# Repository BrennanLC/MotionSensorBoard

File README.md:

Motion Sensor Board
==============

Wireless motion sensor board that interfaces with parallax PIR sensor.
Board uses the Attiny2313A microcontroller. wireless capability provided by Xbee Pro Series 2 module.

Current version of motion sensor board verified on 9/28/14

Files:

MotionSensorsch.pdf - Copy of board schematic in PDF format
MotionSensorBoard.sch - Board schematic eagle file 
MotionSensorBoard.brd - Board layout eagle file
MotionSensorBoard.pdf - Board layout in PDF format
Gerbers.zip - Gerber board files

schematic and board layout built with Eagle 6.4.0 Standard. More info and 
download available here:

https://www.cadsoftusa.com/

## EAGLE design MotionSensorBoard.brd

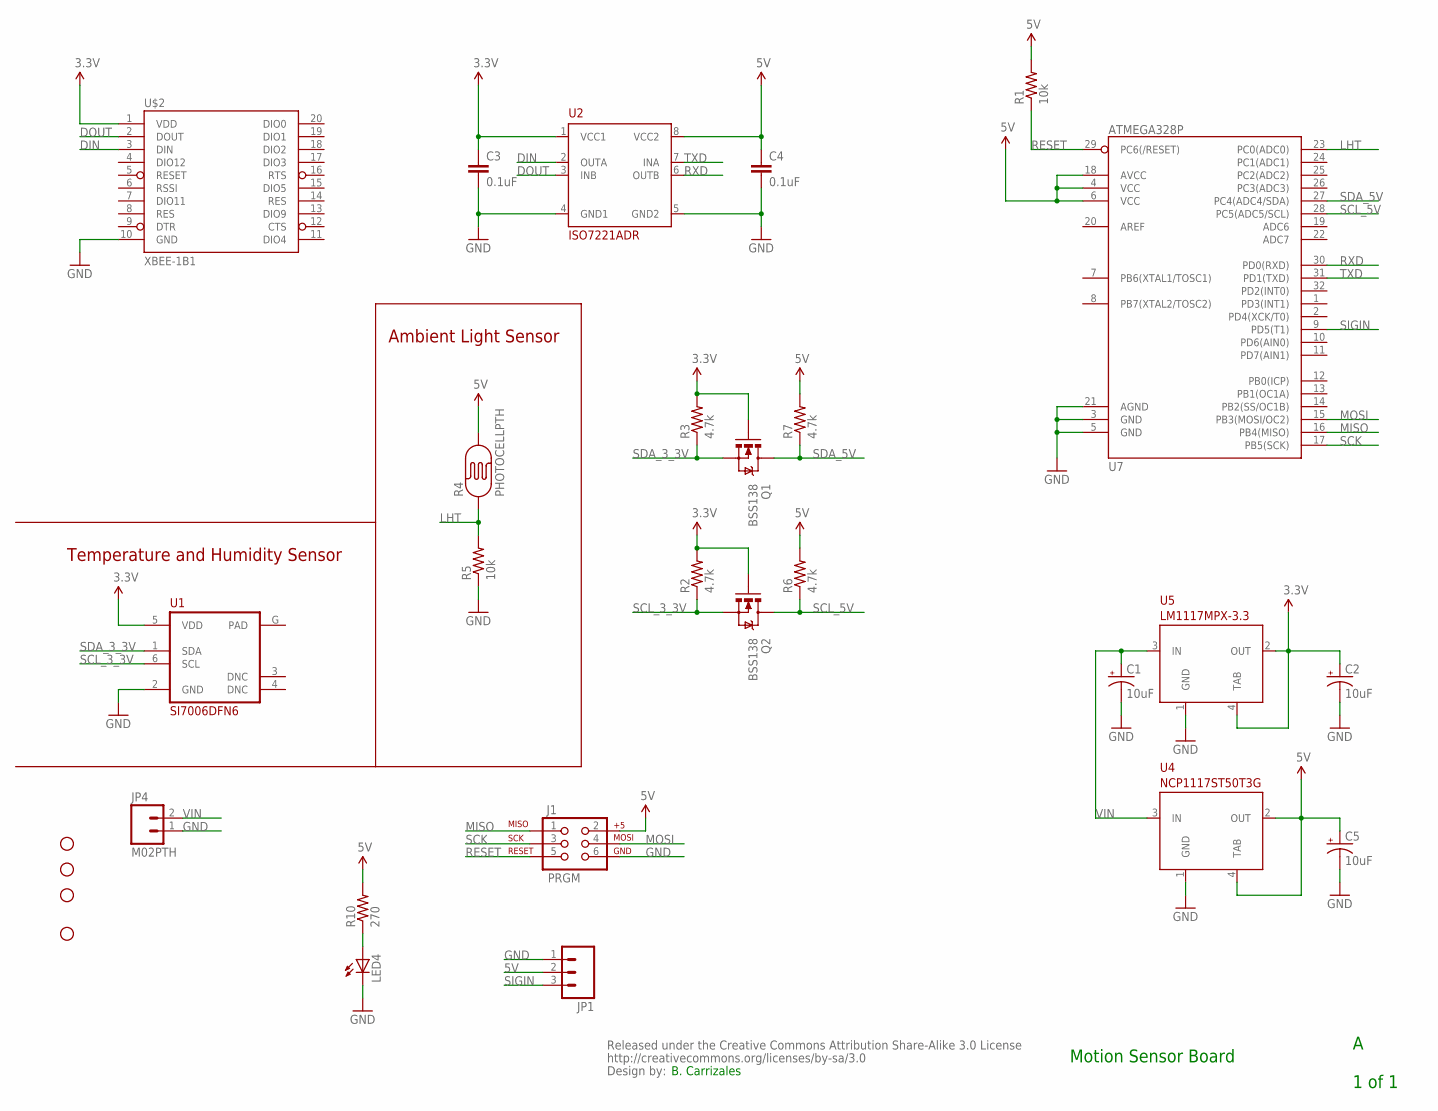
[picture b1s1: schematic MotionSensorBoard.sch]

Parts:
C1, C2, C5: 10uF; EIA6032
C3, C4: 0.1uF; 0603-CAP
CC_TEXT1: CREATIVE_COMMONS
J1: PRGM; 2X3
JP1: M03PTH; 1X03
JP4: M02PTH; 1X02
LED4: LED0603; LED-0603
Q1, Q2: BSS138; SOT23
R1, R5: 10k; 0603-RES
R2, R3, R6, R7: 4.7k; 0603-RES
R4: PHOTOCELLPTH; PHOTOCELL
R10: 270; 0603-RES
STANDOFF1, STANDOFF2, STANDOFF3, STANDOFF4: STAND-OFF
U1: SI7006DFN6; DFN-6
U2: ISO7221ADR; SO08
U4: NCP1117ST50T3G; SOT223
U5: LM1117MPX-3.3; SOT223
U7: ATMEGA328P; TQFP32-08
U$2: XBEE-1B1; XBEE-1

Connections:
3.3V: C2.P$1 (+), C3.1, Q1.1 (G), Q2.1 (G), R2.2, R3.2, U1.5 (VDD), U2.1 (VCC1), U5.2 (OUT), U5.4 (TAB), U$2.1 (VDD)
5V: C4.1, C5.P$1 (+), J1.2, JP1.2, R1.2, R4.2, R6.2, R7.2, R10.2, U2.8 (VCC2), U4.2 (OUT), U4.4 (TAB), U7.4 (VCC), U7.6 (VCC), U7.18 (AVCC)
DIN: U2.2 (OUTA), U$2.3 (DIN)
DOUT: U2.3 (INB), U$2.2 (DOUT)
GND: C1.P$2 (-), C2.P$2 (-), C3.2, C4.2, C5.P$2 (-), J1.6, JP1.1, JP4.1, LED4.C, R5.1, U1.2 (GND), U2.4 (GND1), U2.5 (GND2), U4.1 (GND), U5.1 (GND), U7.3 (GND), U7.5 (GND), U7.21 (AGND), U$2.10 (GND)
LHT: R4.1, R5.2, U7.23 (PC0(ADC0))
MISO: J1.1, U7.16 (PB4(MISO))
MOSI: J1.4, U7.15 (PB3(MOSI/OC2))
unnamed: LED4.A, R10.1
RESET: J1.5, R1.1, U7.29 (PC6(/RESET))
RXD: U2.6 (OUTB), U7.30 (PD0(RXD))
SCK: J1.3, U7.17 (PB5(SCK))
SCL_3_3V: Q2.2 (S), R2.1, U1.6 (SCL)
SCL_5V: Q2.3 (D), R6.1, U7.28 (PC5(ADC5/SCL))
SDA_3_3V: Q1.2 (S), R3.1, U1.1 (SDA)
SDA_5V: Q1.3 (D), R7.1, U7.27 (PC4(ADC4/SDA))
SIGIN: JP1.3, U7.9 (PD5(T1))
TXD: U2.7 (INA), U7.31 (PD1(TXD))
VIN: C1.P$1 (+), JP4.2, U4.3 (IN), U5.3 (IN)

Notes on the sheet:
Motion Sensor Board
1 of 1
B. Carrizales
Temperature and Humidity Sensor
Ambient Light Sensor

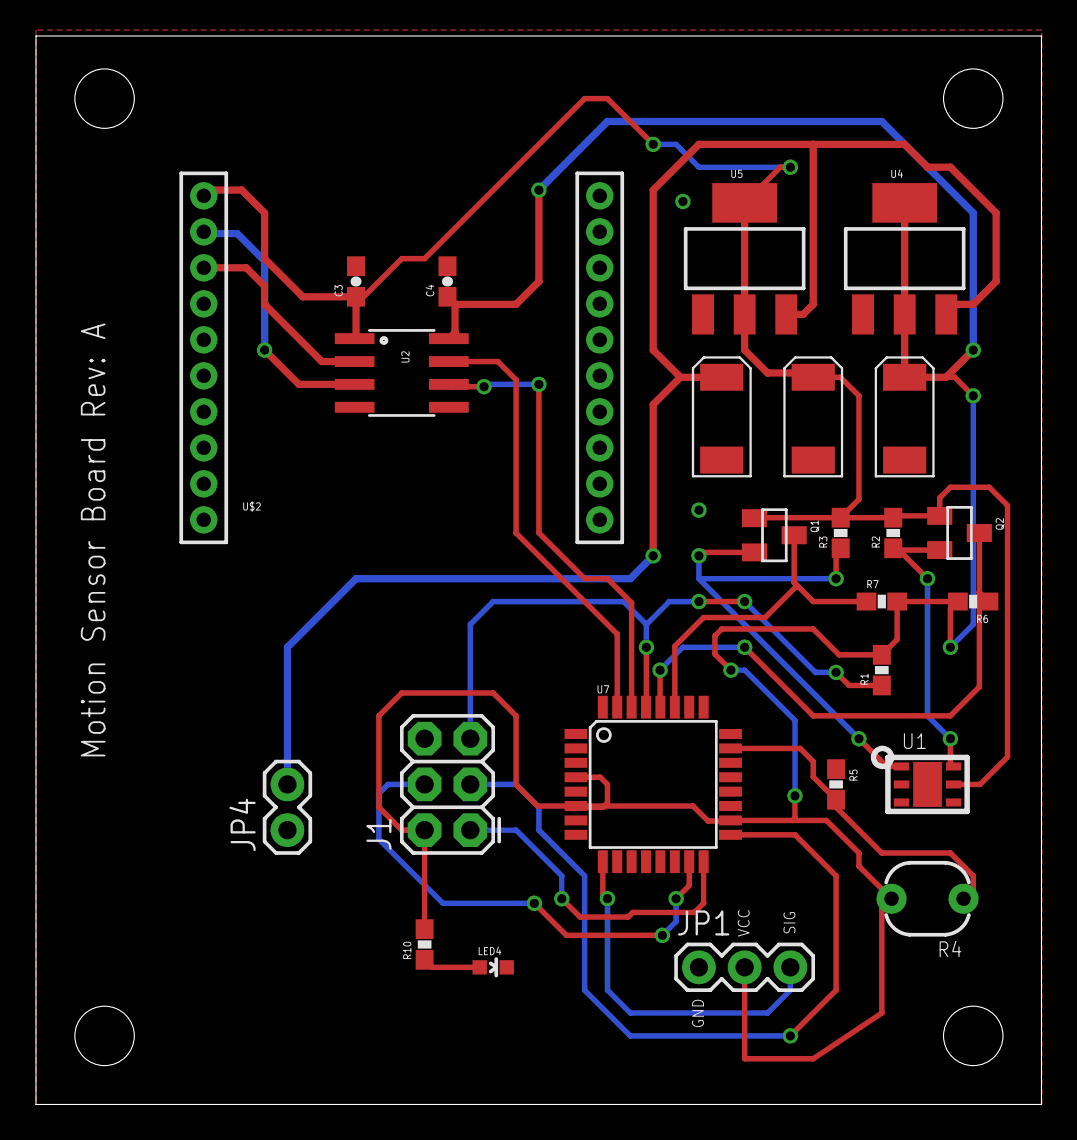
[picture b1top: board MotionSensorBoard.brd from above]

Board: 2 copper layers, 55.9 x 59.4 mm, 30 parts (0 on the bottom side), 19 nets.

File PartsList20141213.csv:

"Part";"Value";"Device";"Package";"Description";"DIGIKEYPART#";"PROD_ID";"VALUE";
"C1";"10uF";"CAP_POL_AL";"PANASONIC_BMIN";"Panasonic Aluminum Electrolytic Capacitor Package B";"";"";"";
"C2";"10uF";"CAP_POL_AL";"PANASONIC_BMIN";"Panasonic Aluminum Electrolytic Capacitor Package B";"";"";"";
"C3";"0.1uF";"CAP0603-CAP";"0603-CAP";"Capacitor";"";"";"";
"C4";"0.1uF";"CAP0603-CAP";"0603-CAP";"Capacitor";"";"";"";
"C7";"10uF";"CAP_POL_AL";"PANASONIC_BMIN";"Panasonic Aluminum Electrolytic Capacitor Package B";"";"";"";
"J1";"PRGM";"AVR_SPI_PRG_6PTH";"2X3";"AVR ISP 6 Pin";"";"";"";
"J2";"POWER_JACKPTH";"POWER_JACKPTH";"POWER_JACK_PTH";"Power Jack";"";"";"";
"JP1";"";"M03PTH";"1X03";"Header 3";"";"";"";
"JP4";"M02PTH";"M02PTH";"1X02";"Standard 2-pin 0.1 header. Use with";"";"";"";
"LED4";"";"LED0603";"LED-0603";"LEDs";"";"";"";
"Q1";"BSS138";"MOSFET-NCHANNELBSS123LT1G";"SOT23";"Common NMOSFET Parts";"";"TRANS-08345";"";
"Q2";"BSS138";"MOSFET-NCHANNELBSS123LT1G";"SOT23";"Common NMOSFET Parts";"";"TRANS-08345";"";
"R1";"10k";"RESISTOR0603-RES";"0603-RES";"Resistor";"";"";"";
"R2";"4.7k";"RESISTOR0603";"0603-RES";"Resistor";"";"";"";
"R3";"4.7k";"RESISTOR0603";"0603-RES";"Resistor";"";"";"";
"R4";"PHOTOCELLPTH";"PHOTOCELLPTH";"PHOTOCELL";"CdS photoresistor. This is a low cost way to detect light levels. Resistance decreases with more incoming light. SparkFun SKU: SEN-09088";"";"";"";
"R5";"10k";"RESISTOR0603";"0603-RES";"Resistor";"";"";"";
"R6";"4.7k";"RESISTOR0603";"0603-RES";"Resistor";"";"";"";
"R7";"4.7k";"RESISTOR0603";"0603-RES";"Resistor";"";"";"";
"R10";"270";"RESISTOR0603-RES";"0603-RES";"Resistor";"";"";"";
"STANDOFF1";"STAND-OFF";"STAND-OFF";"STAND-OFF";"#4 Stand Off";"";"";"";
"STANDOFF2";"STAND-OFF";"STAND-OFF";"STAND-OFF";"#4 Stand Off";"";"";"";
"STANDOFF3";"STAND-OFF";"STAND-OFF";"STAND-OFF";"#4 Stand Off";"";"";"";
"STANDOFF4";"STAND-OFF";"STAND-OFF";"STAND-OFF";"#4 Stand Off";"";"";"";
"U$2";"XBEE-1B1";"XBEE-1B1";"XBEE-1";"Xbee module footprints";"";"";"";
"U2";"ISO7221ADR";"ISO7221ADR";"SO08";"ISO7221 Dual Channel Digital Isolator from Texas Instruments. See Datasheet for more info Datasheet";"296-21955-1-ND";"";"";
"U3";"BMP180";"BMP180";"BMP180";"BOSCH BMP180 DIGITAL BAROMETRIC PRESSURE SENSOR";"";"";"";
"U4";"NCP1117ST50T3G";"NCP1117ST50T3G";"SOT223";"NCP1117 5V, 1.0 A Low-Dropout Positive Fixed and Adjustable Voltage Regulator  Datasheet";"NCP1117ST50T3GOSCT-ND";"";"";
"U5";"LM1117MPX-3.3";"LM1117MPX-3.3";"SOT223";"3.3V Low Dropout Regulator, 0.8A output. See datasheet for more info Datasheet";"LM1117MPX-3.3/NOPBCT-ND";"";"";
"U6";"HTU21DSMD";"HTU21DSMD";"HTU21D";"";"";"";"";
"U7";"ATMEGA328P";"ATMEGA328_SMT";"TQFP32-08";"32-Pin Atmega328 part";"";"IC-09069";"ATMEGA328P";

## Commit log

2014-02-20 Initial Commit
    Initial Commit
2014-02-27 Added Gerber Files
2014-10-01 Update README.md
    Board fully verified
2014-11-15 updated schematic
2014-11-16 Schematic Updated
    Schematic Rev A major revisions complete
2015-02-03 updated board layout and generated Gerbers
2015-02-14 updated parts list
2015-02-16 generated pdf

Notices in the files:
parts and their libraries:
SparkFun-Electromechanical: Licensing: CC v3.0 Share-Alike You are welcome to use this library for commercial purposes.
SparkFun-Aesthetics: Released under the Creative Commons Attribution Share-Alike 3.0 License
SparkFun-Aesthetics: http://creativecommons.org/licenses/by-sa/3.0
